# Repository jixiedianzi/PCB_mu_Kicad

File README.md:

# PCB_mu_Kicad
## 买手台加下面qq
* 1318066615

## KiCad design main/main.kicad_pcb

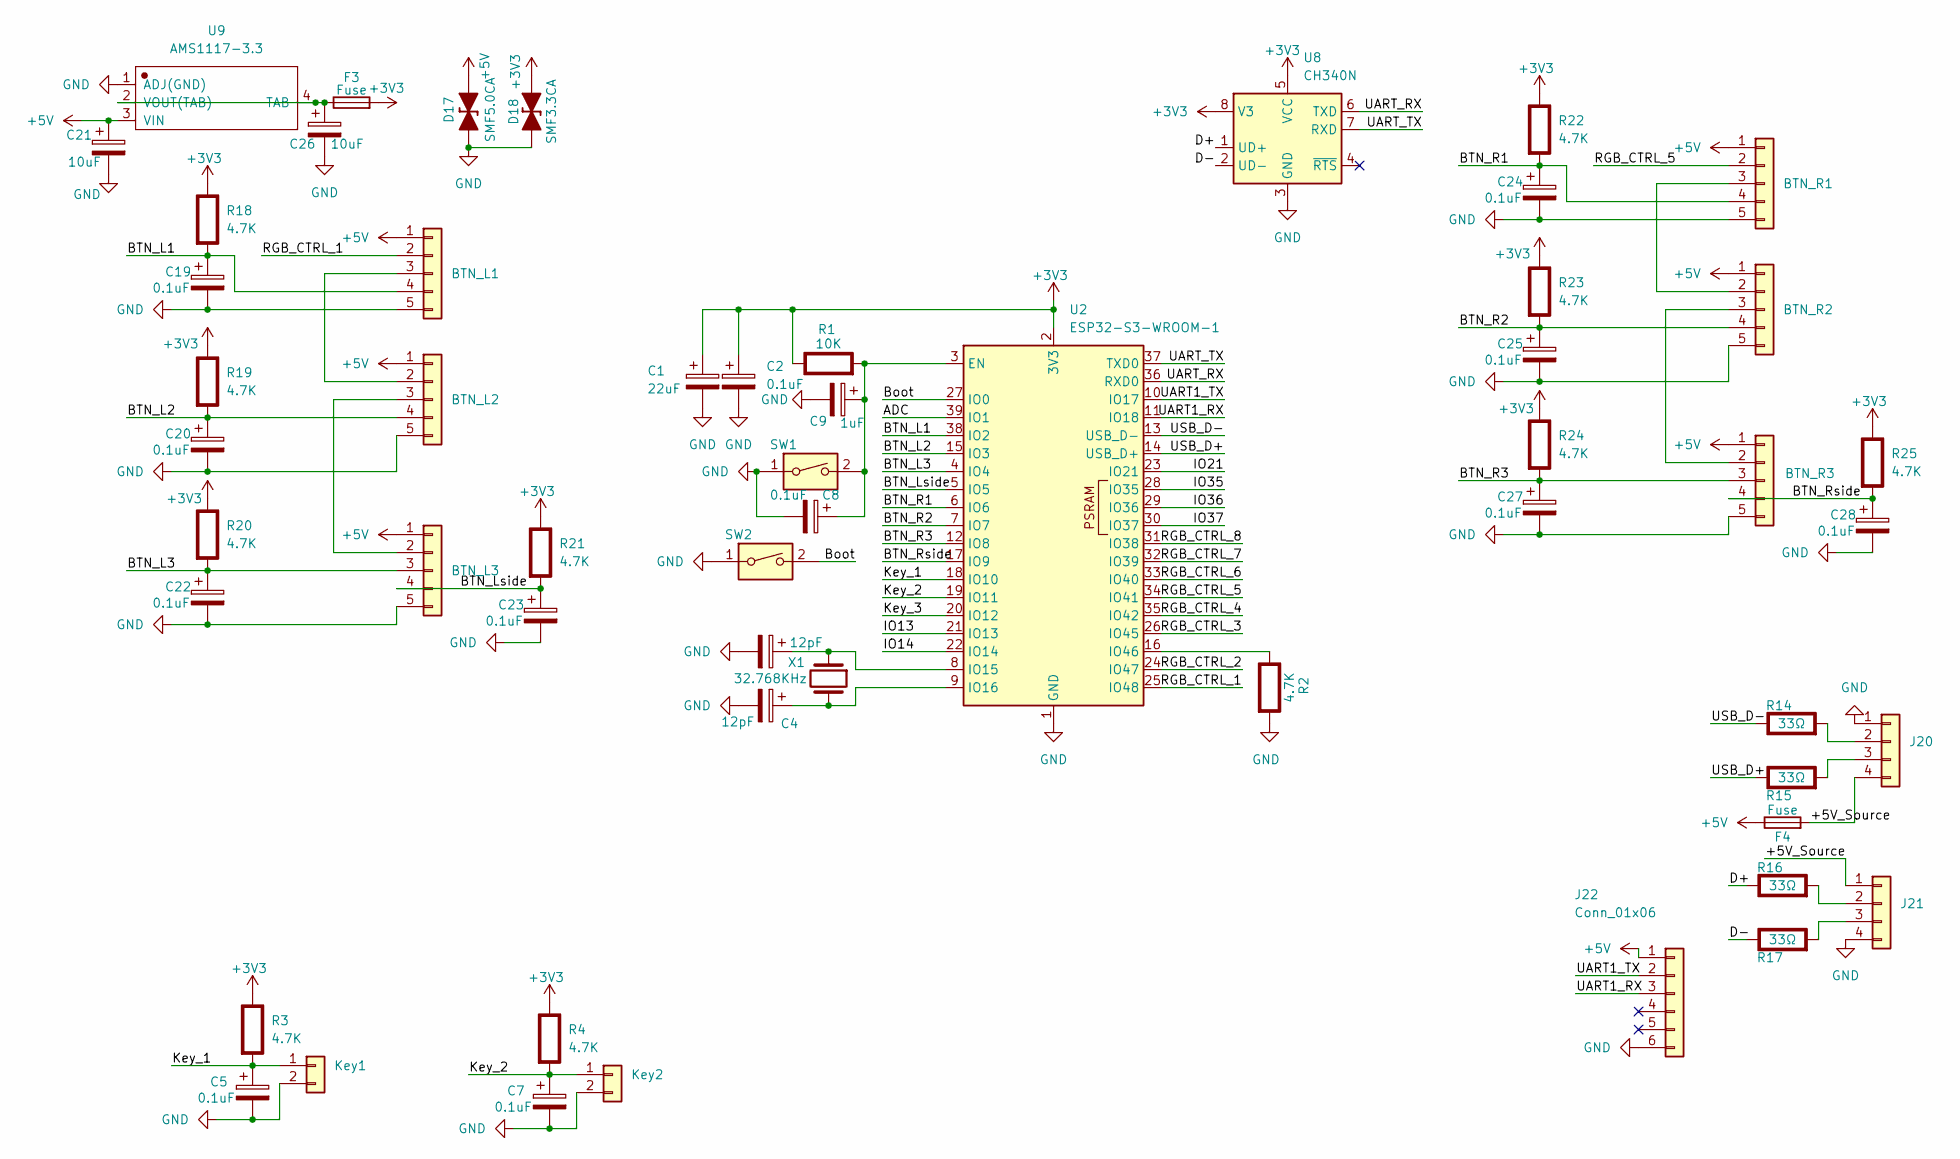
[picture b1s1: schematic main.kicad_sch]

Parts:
BTN_L1, BTN_L2, BTN_L3: Conn_01x05; JST_XH_B5B-XH-AM_1x05_P2.50mm_Vertical
BTN_R1, BTN_R2, BTN_R3: Conn_01x05; JST_XH_B5B-XH-AM_1x05_P2.50mm_Vertical
C1: 22uF; C_0805_2012Metric
C2, C5, C7, C8, C19, C20, C22, C23, C24, C25, C27, C28: 0.1uF; C_0603_1608Metric_Pad1.08x0.95mm_HandSolder
C3, C4: 12pF; C_0603_1608Metric_Pad1.08x0.95mm_HandSolder
C9: 1uF; C_0805_2012Metric_Pad1.18x1.45mm_HandSolder
C21, C26: 10uF; C_0805_2012Metric_Pad1.18x1.45mm_HandSolder
D17: SMF5.0CA; D_SOD-123F
D18: SMF3.3CA; D_SOD-123F
F3, F4: Fuse; Fuse_1206_3216Metric
J20: Conn_01x04; JST_XH_B4B-XH-A_1x04_P2.50mm_Vertical
J21: Conn_01x04; PinHeader_1x04_P2.54mm_Vertical
J22: Conn_01x06; JST_SH_BM06B-SRSS-TB_1x06-1MP_P1.00mm_Vertical
Key1, Key2: Conn_01x02; JST_XH_B2B-XH-AM_1x02_P2.50mm_Vertical
R1: 10K; R_1206_3216Metric_Pad1.30x1.75mm_HandSolder; Rating W
R2, R3, R4, R18, R19, R20, R21, R22, R23, R24, R25: 4.7K; R_0805_2012Metric; Rating W
R14, R15, R16, R17: 33Ω; R_0805_2012Metric; Rating W
SW1, SW2: SW_DIP_x01; SW_SPST_EVQPE1
U2: ESP32-S3-WROOM-1
U8: CH340N; SOP-8_3.9x4.9mm_P1.27mm
U9: AMS1117-3.3; SOT-223-4_L6.5-W3.5-P2.30-LS7.0-BR
X1: 32.768KHz; Crystal_DS10_D1.0mm_L4.3mm_Vertical

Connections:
+3V3: C1.1, C2.1, D18.2 (A), F3.2, R1.1 (+), R3.1 (+), R4.1 (+), R18.1 (+), R19.1 (+), R20.1 (+), R21.1 (+), R22.1 (+), R23.1 (+), R24.1 (+), R25.1 (+), U2.2 (3V3), U8.5 (VCC), U8.8 (V3)
+5V: BTN_L1.1, BTN_L2.1, BTN_L3.1, BTN_R1.1, BTN_R2.1, BTN_R3.1, C21.1, D17.2 (A), F4.1, J22.1, U9.3 (VIN)
/+5V_Source: F4.2, J20.4, J21.1
/ADC: U2.39 (IO1)
/BTN_L1: BTN_L1.4, C19.1, R18.2 (-), U2.38 (IO2)
/BTN_L2: BTN_L2.4, C20.1, R19.2 (-), U2.15 (IO3)
/BTN_L3: BTN_L3.3, C22.1, R20.2 (-), U2.4 (IO4)
/BTN_Lside: BTN_L3.4, C23.1, R21.2 (-), U2.5 (IO5)
/BTN_R1: BTN_R1.4, C24.1, R22.2 (-), U2.6 (IO6)
/BTN_R2: BTN_R2.4, C25.1, R23.2 (-), U2.7 (IO7)
/BTN_R3: BTN_R3.3, C27.1, R24.2 (-), U2.12 (IO8)
/BTN_Rside: BTN_R3.4, C28.1, R25.2 (-), U2.17 (IO9)
/Boot: SW2.2, U2.27 (IO0)
/D+: R16.1 (+), U8.1 (UD+)
/D-: R17.1 (+), U8.2 (UD-)
/IO13: U2.21 (IO13)
/IO14: U2.22 (IO14)
/IO21: U2.23 (IO21)
/IO35: U2.28 (IO35)
/IO36: U2.29 (IO36)
/IO37: U2.30 (IO37)
/Key_1: C5.1, Key1.1, R3.2 (-), U2.18 (IO10)
/Key_2: C7.1, Key2.1, R4.2 (-), U2.19 (IO11)
/Key_3: U2.20 (IO12)
/RGB_CTRL_1: BTN_L1.2, U2.25 (IO48)
/RGB_CTRL_2: U2.24 (IO47)
/RGB_CTRL_3: U2.26 (IO45)
/RGB_CTRL_4: U2.35 (IO42)
/RGB_CTRL_5: BTN_R1.2, U2.34 (IO41)
/RGB_CTRL_6: U2.33 (IO40)
/RGB_CTRL_7: U2.32 (IO39)
/RGB_CTRL_8: U2.31 (IO38)
/UART1_RX: J22.3, U2.11 (IO18)
/UART1_TX: J22.2, U2.10 (IO17)
/UART_RX: U2.36 (RXD0), U8.6 (TXD)
/UART_TX: U2.37 (TXD0), U8.7 (RXD)
/USB_D+: R15.1 (+), U2.14 (USB_D+)
/USB_D-: R14.1 (+), U2.13 (USB_D-)
GND: BTN_L1.5, BTN_L2.5, BTN_L3.5, BTN_R1.5, BTN_R2.5, BTN_R3.5, C1.2, C2.2, C3.2, C4.2, C5.2, C7.2, C8.2, C9.2, C19.2, C20.2, C21.2, C22.2, C23.2, C24.2, C25.2, C26.2, C27.2, C28.2, D17.1 (K), D18.1 (K), J20.1, J21.4, J22.6, Key1.2, Key2.2, R2.2 (-), SW1.1, SW2.1, U2.1 (GND), U2.40 (GND), U2.41 (GND), U8.3 (GND), U9.1 (ADJ(GND))
unnamed: BTN_L1.3, BTN_L2.2
unnamed: BTN_L2.3, BTN_L3.2
unnamed: BTN_R1.3, BTN_R2.2
unnamed: BTN_R2.3, BTN_R3.2
unnamed: J20.2, R14.2 (-)
unnamed: J20.3, R15.2 (-)
unnamed: J21.2, R16.2 (-)
unnamed: J21.3, R17.2 (-)
unnamed: C8.1, C9.1, R1.2 (-), SW1.2, U2.3 (EN)
unnamed: R2.1 (+), U2.16 (IO46)
unnamed: C3.1, U2.8 (IO15), X1.1
unnamed: C4.1, U2.9 (IO16), X1.2
unnamed: C26.1, F3.1, U9.2 (VOUT(TAB)), U9.4 (TAB)

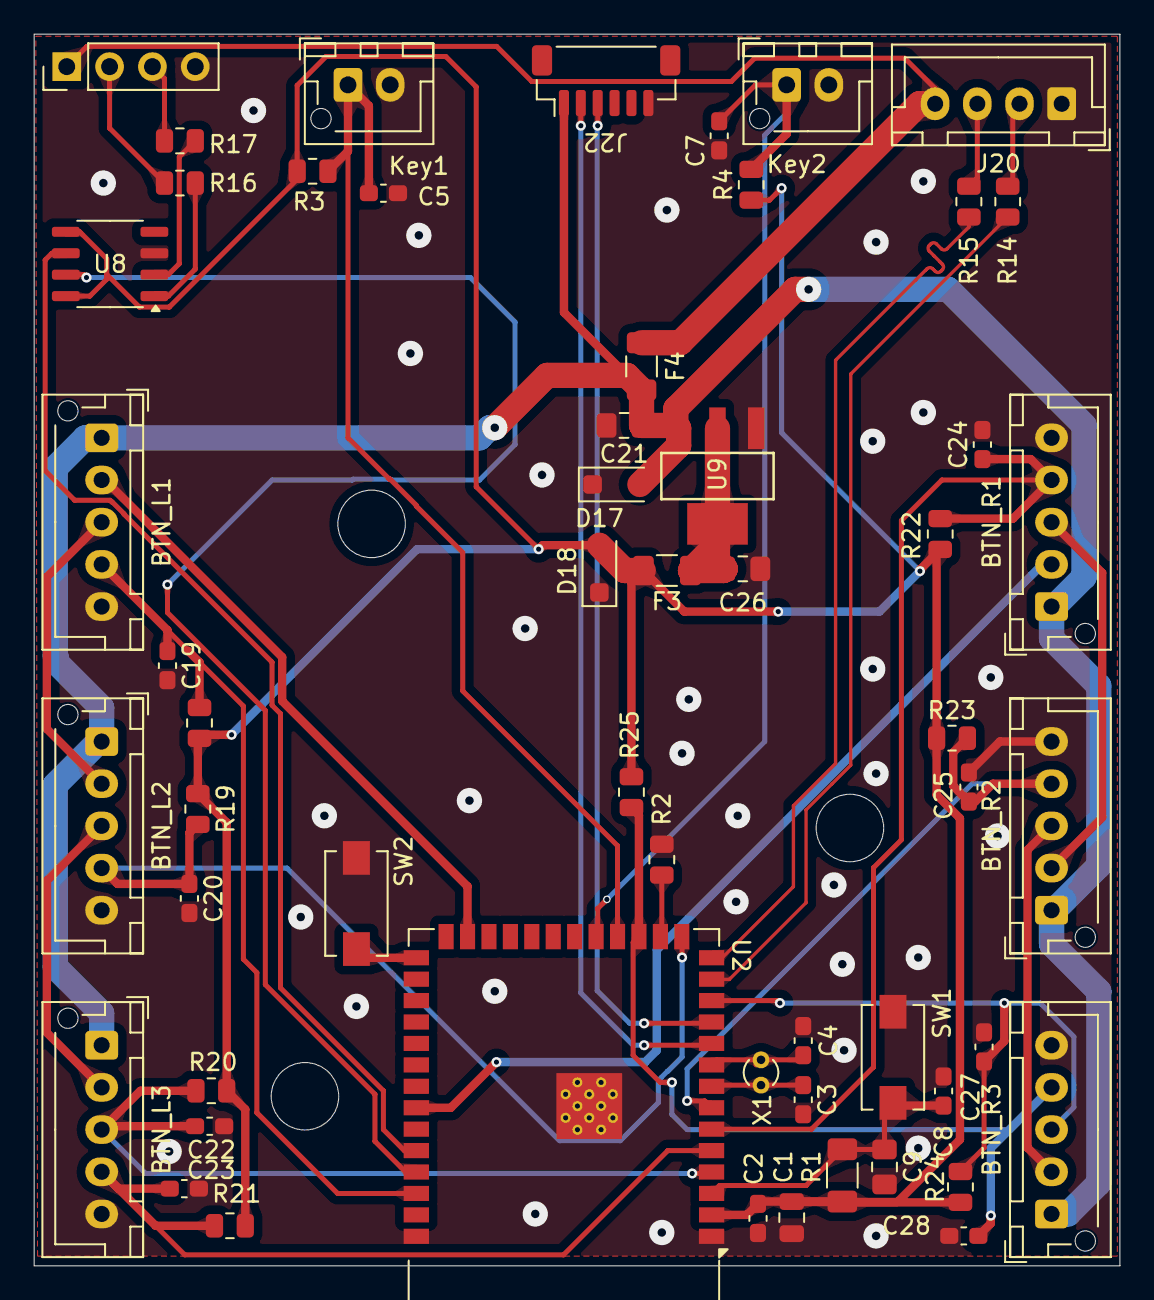
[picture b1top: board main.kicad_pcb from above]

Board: 2 copper layers, 64.4 x 73.0 mm, 55 parts (0 on the bottom side), 38 nets.

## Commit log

2025-07-13 V1.0
2025-11-01 V1.1
2025-11-26 V1.2
2025-12-14 V1.21
